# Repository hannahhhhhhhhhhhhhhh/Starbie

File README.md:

# Starbie !

Starbie is a custom gun shaped digital pet designed in KiCad.
It features an OLED display that shows a character, which reacts to its environment using onboard sensors. 
The MPU6050 accelerometer and gyroscope module detects movement and orientation, allowing the character to respond when the badge is tilted or shaken. 
The DHT11 sensor reads the surrounding temperature and humidity, which can influence how the character behaves or what gets displayed on screen. 
Two push buttons allow the user to manually interact with the badge. 
All components communicate with the ESP32-C3 over I2C or direct GPIO pins as defined in the schematic, and the board is powered over USB-C through the XIAO module.

---

## Screenshots of the schematic and pcb editor <3

## Hardware Specifications & Component List
To fully assemble the Starbie PCB,  the following components are needed:

*   **Microcontroller:** 1x Seeed Studio XIAO-ESP32-C3
*   **Sensors:** 
    *   1x DHT11 Environment Sensor (Temperature & Humidity)
    *   1x MPU6050 6-Axis Motion Tracking Module (Accelerometer & Gyroscope)
*   **Display:** 1x I2C OLED Display Module (4-pin setup: VCC, GND, SCL, SDA)
*   **Discreet Components:**
    *   2x 6x6mm Tactile Push Buttons (SW_Push)
    *   1x 10kΩ Axial Resistor (Pull-up for DHT11 data line)

---

##  Project Structure Info
*   `/starbie.kicad_pro` - Main KiCad project configuration file.
*   `/starbie.kicad_pcb` - 2-layer gun shaped PCB layout file.
*   `/starbie.kicad_sch` - Schematic capture file mapping the components and I2C buses.

Also included the gerber files for the pcb
---
## Why I Made This

I think a digital pet is a really cool concept and that we can code it based on our interests so I mostly followed the idea of the tutorial, but also I wanted it to look and act different which is why I designed it differently. I had a lot of fun making this project and learned a lot about kicad.

## Firmware Flashing Guide

### You Need:
- Arduino IDE
- ESP32 board package installed in Arduino IDE
- USB-C cable
- Install the ESP32 Board Package

### Connecting the Board
1. Plug the XIAO ESP32-C3 into your computer via USB-C
2. Wait for drivers to install

### Selecting the Board in Arduino IDE
1. Go to Tools > Board > esp32 > XIAO_ESP32C3
2. Go to Tools > Port and select the port that appeared when you 
   plugged in the board 

### Upload Sketch
1. Open `Starbie.ino` in Arduino IDE
2. Click the Upload button
3. Wait for "Done uploading" to appear
4. Done!!

## Bill of Materials

| Component | Quantity | Unit Price (CAD) | Total Price (CAD) |
|-----------|----------|------------------|-------------------|
| XIAO ESP32-C3 | 1 | $8.50 | $8.50 |
| Push Button (SW_Push) | 2 | $2.79 | $5.58 |
| 0.96in OLED Display 4-pin I2C | 1 | $3.50 | $3.50 |
| MPU6050 Accelerometer Module | 1 | $2.70 | $2.70 |
| DHT11 Temperature Humidity Sensor | 1 | $2.16 | $2.16 |
| PCB Fabrication (JLCPCB) | 1 | $14.68 | $14.68 |
| | | **Total** | **$37.12** |

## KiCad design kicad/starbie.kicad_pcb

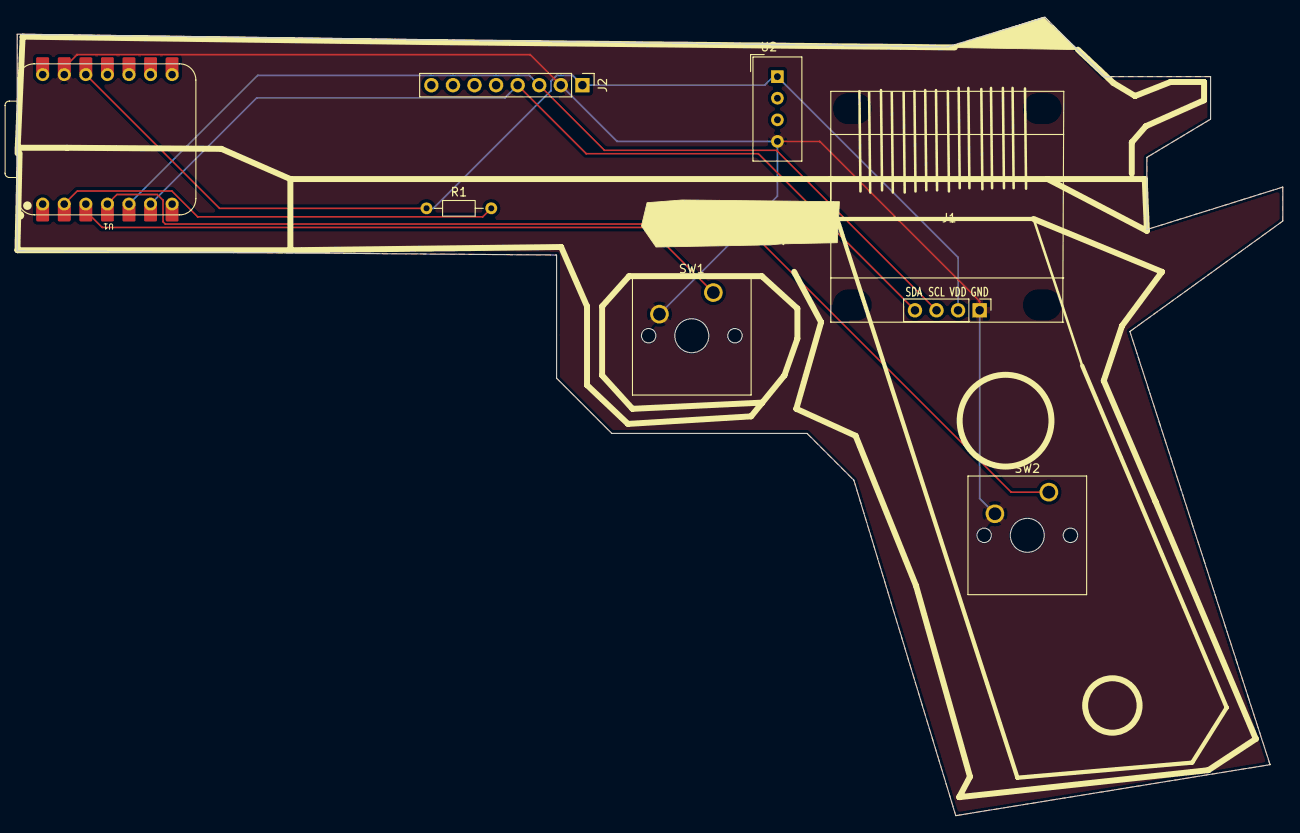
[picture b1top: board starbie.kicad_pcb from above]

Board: 2 copper layers, 149.0 x 94.0 mm, 7 parts (0 on the bottom side), 7 nets.

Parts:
J1: Conn_01x04_Pin; Display_128x64_096_I2C
J2: Conn_01x08_Pin; PinHeader_1x08_P2.54mm_Vertical
R1: 10k; R_Axial_DIN0204_L3.6mm_D1.6mm_P7.62mm_Horizontal
SW1, SW2: SW_Push; SW_Cherry_MX_1.00u_PCB
U1: XIAO-ESP32-C3-SMD; XIAO-ESP32-C6-DIP
U2: DHT11; Aosong_DHT11_5.5x12.0_P2.54mm

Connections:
+3.3V: J1.2, J2.1, R1.1, U1.12 (3V3_OUT), U2.1 (VDD)
/DHT11 DATA: R1.2, U1.2 (D1)
/GPIO2: SW1.1, U1.3 (D2)
/GPIO3: SW2.1, U1.4 (D3)
/SCL: J1.3, J2.3, U1.5 (D4)
/SDA: J1.4, J2.4, U1.6 (D5)
GND: J1.1, J2.2, SW1.2, SW2.2, U1.13 (GND), U2.4 (GND)
